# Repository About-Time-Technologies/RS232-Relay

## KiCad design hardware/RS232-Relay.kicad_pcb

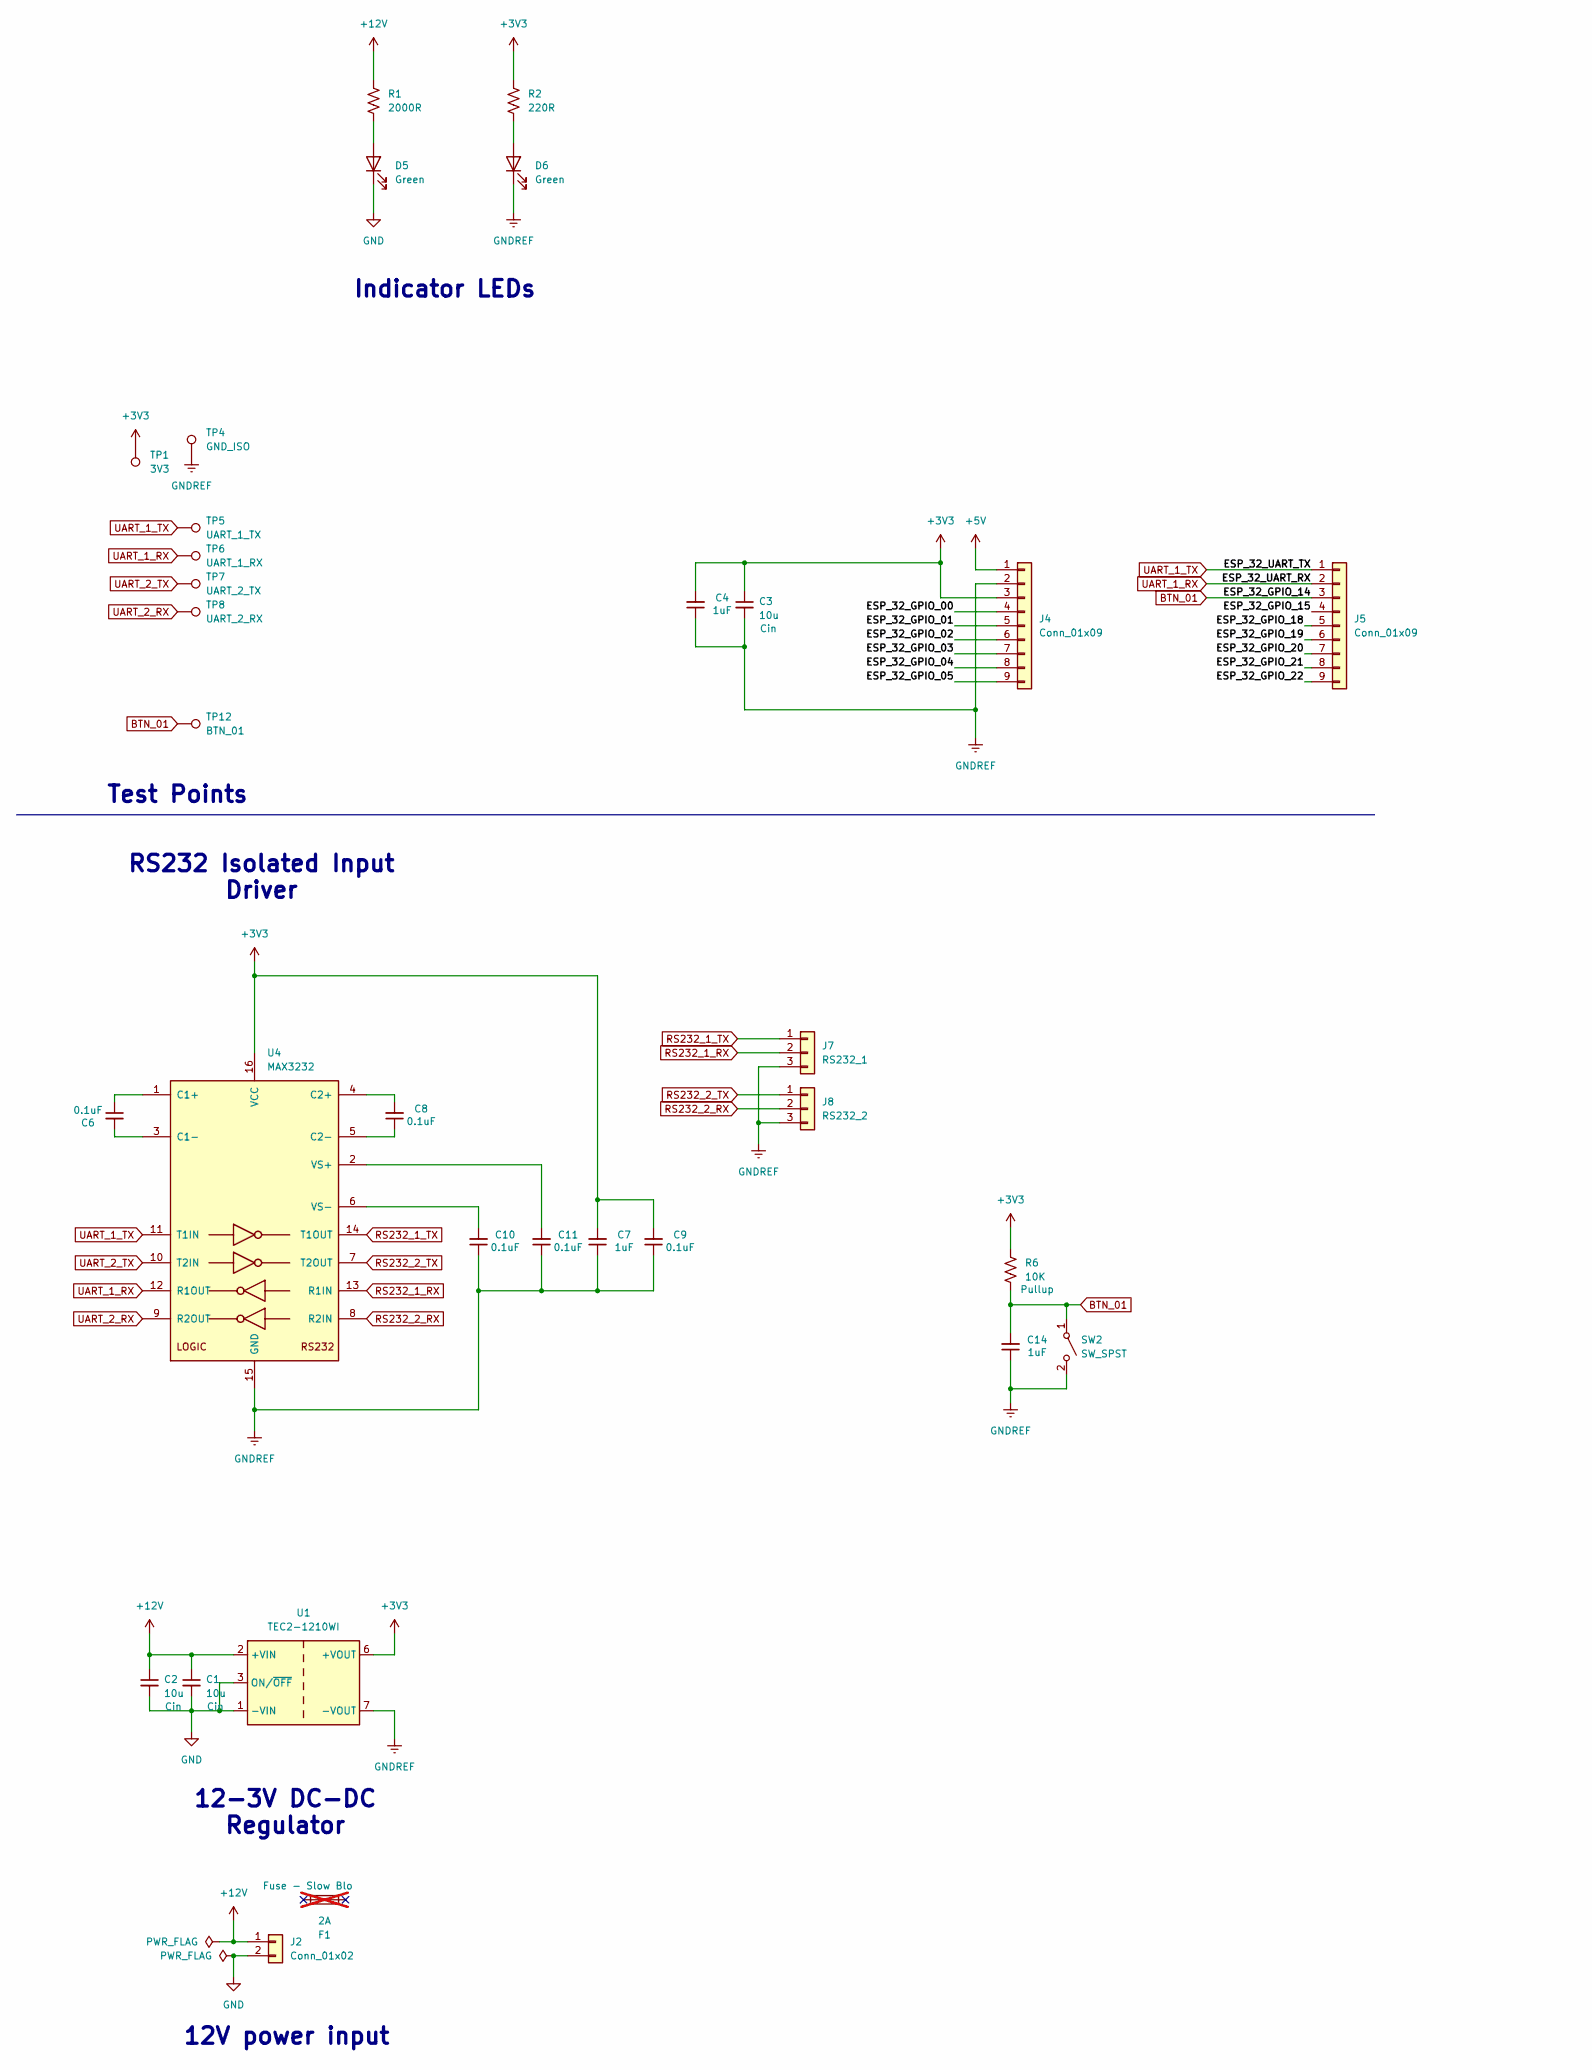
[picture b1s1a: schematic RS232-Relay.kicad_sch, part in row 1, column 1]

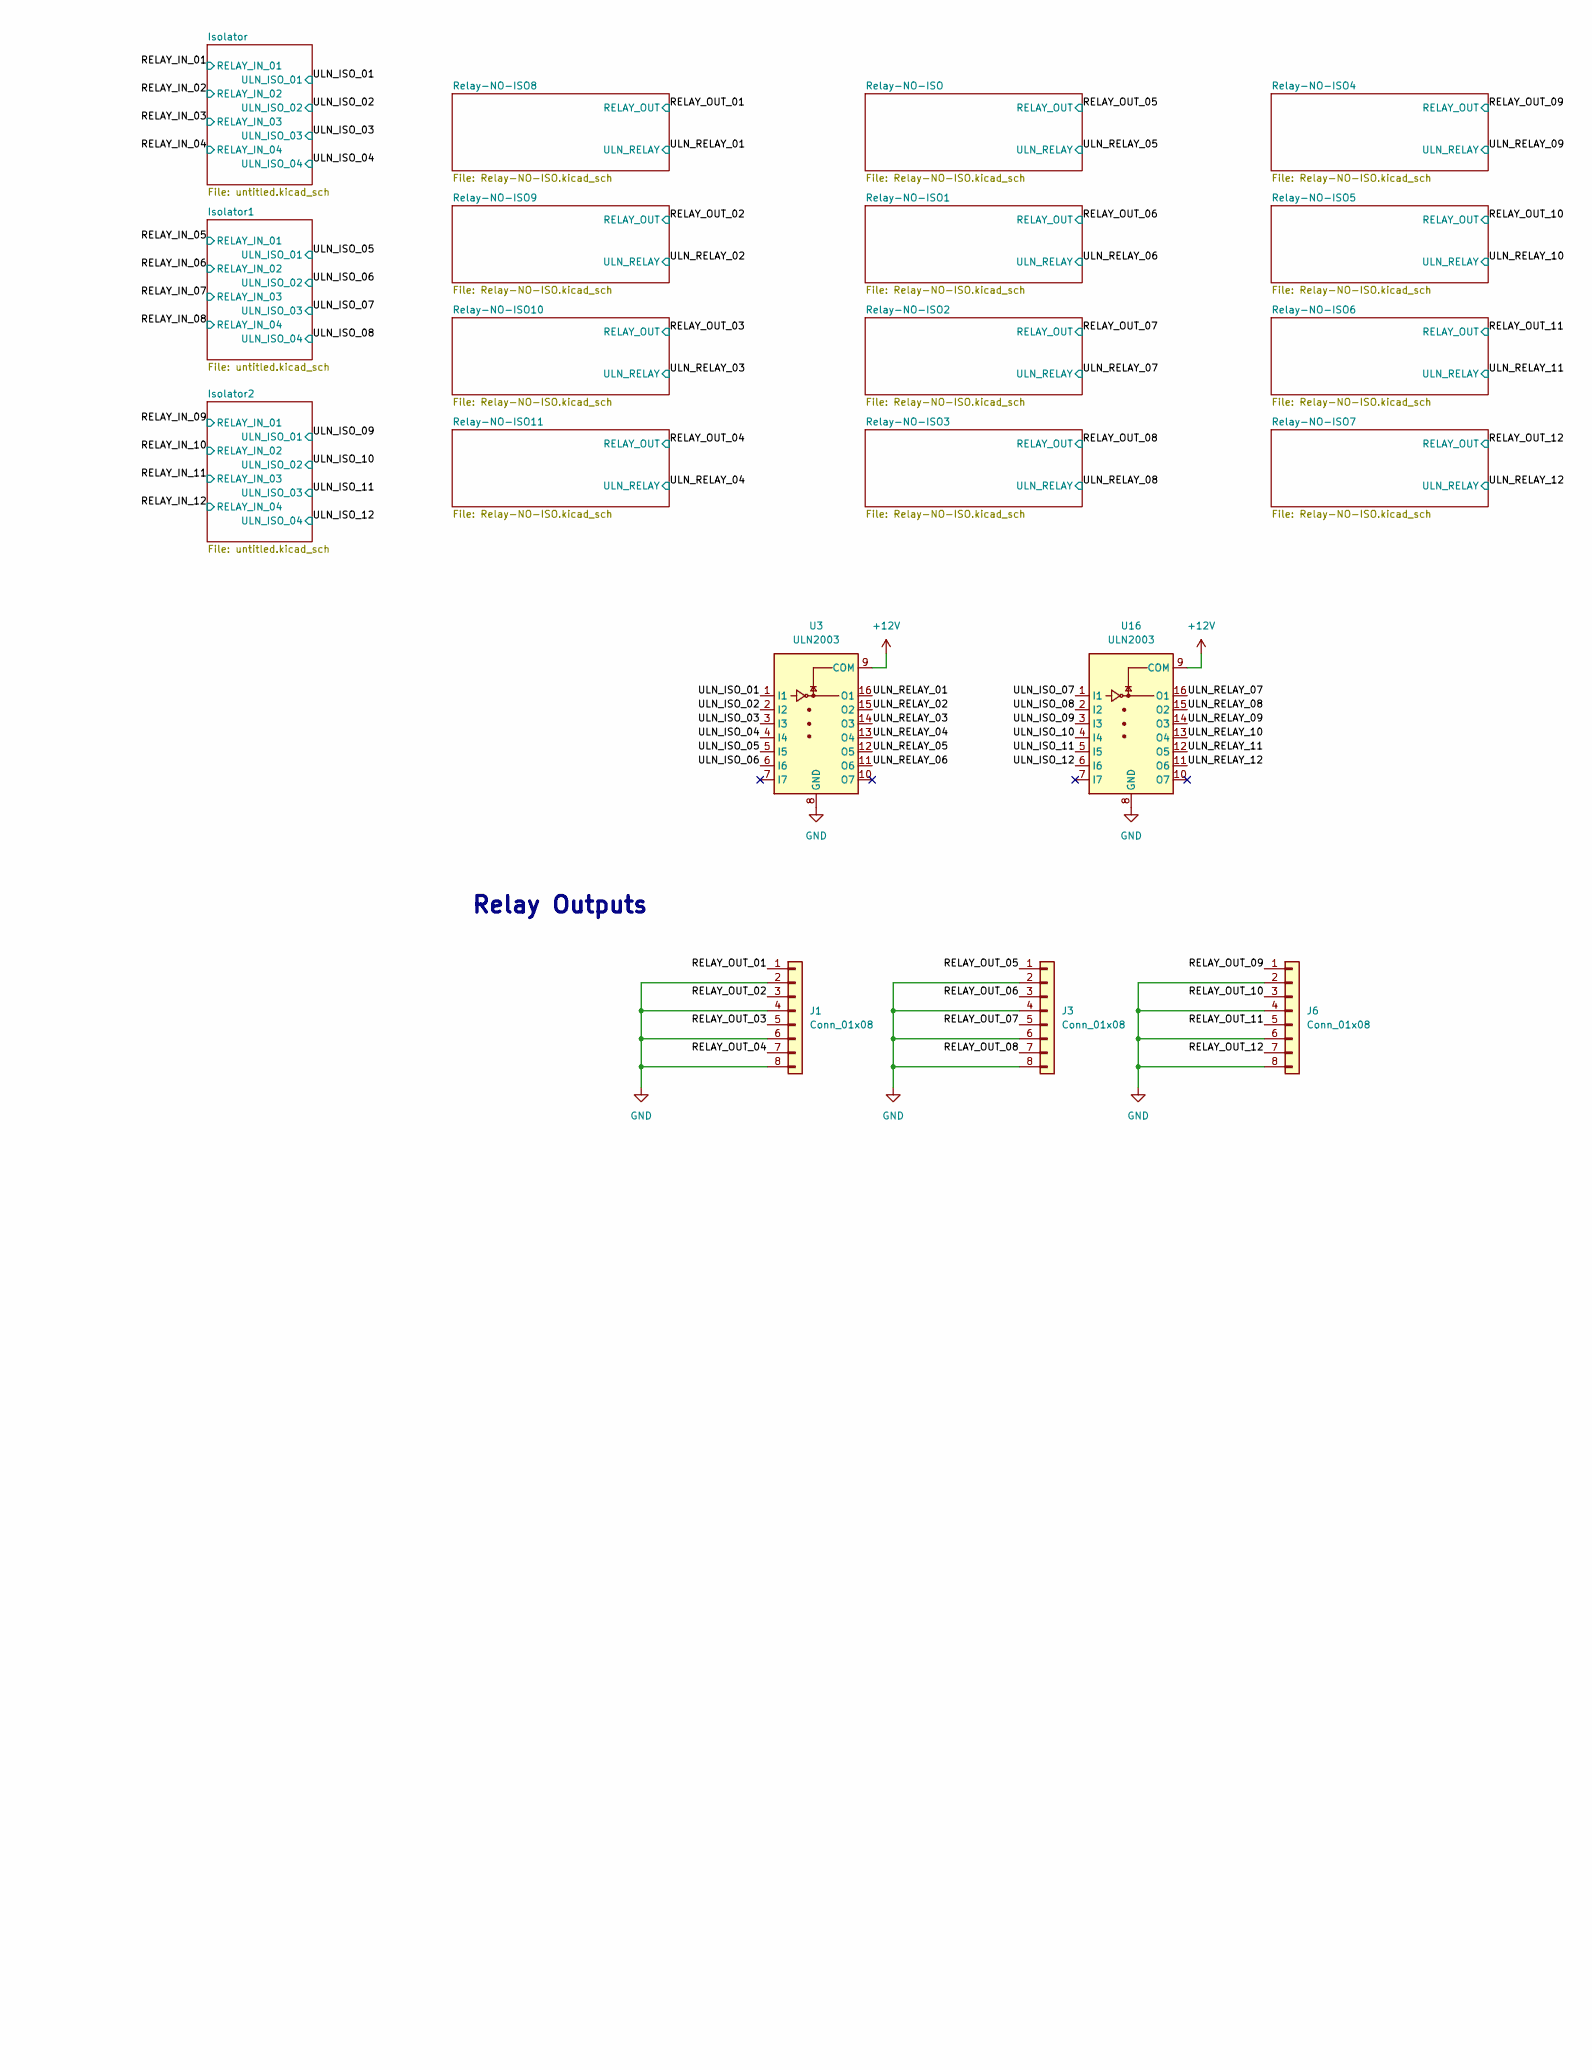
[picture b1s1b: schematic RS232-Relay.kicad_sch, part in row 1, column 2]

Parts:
C1, C2, C3: 10u; C_0603_1608Metric; LCSC C19702
C4, C7, C14: 1uF; C_0402_1005Metric; LCSC C52923
C6, C8, C9, C10, C11: 0.1uF; C_0402_1005Metric; LCSC C307331
D5, D6: Green; LED_0805_2012Metric; LCSC C2297
F1: 2A; Fuseholder_Littelfuse_Nano2_154x; not fitted
J1, J3, J6: Conn_01x08; PhoenixContact_MSTBA_2,5_8-G-5,08_1x08_P5.08mm_Horizontal
J2: Conn_01x02; PhoenixContact_MSTBA_2,5_2-G-5,08_1x02_P5.08mm_Horizontal
J4, J5: Conn_01x09; PinSocket_1x09_P2.54mm_Vertical
J7: RS232_1; PhoenixContact_MSTBA_2,5_3-G-5,08_1x03_P5.08mm_Horizontal
J8: RS232_2; PhoenixContact_MSTBA_2,5_3-G-5,08_1x03_P5.08mm_Horizontal
R1: 2000R; R_0603_1608Metric; LCSC C22975
R2: 220R; R_0603_1608Metric; LCSC C22962
R6: 10K; R_0402_1005Metric; LCSC C25744
SW2: SW_SPST; SW_PUSH_1P1T_6x3.5mm_H4.3_APEM_MJTP1243
TP1: 3V3; TestPoint_Pad_D1.0mm
TP4: GND_ISO; TestPoint_Pad_D1.0mm
TP5: UART_1_TX; TestPoint_Pad_D1.0mm
TP6: UART_1_RX; TestPoint_Pad_D1.0mm
TP7: UART_2_TX; TestPoint_Pad_D1.0mm
TP8: UART_2_RX; TestPoint_Pad_D1.0mm
TP12: BTN_01; TestPoint_Pad_D1.0mm
U1: TEC2-1210WI; Converter_DCDC_TRACO_TMR-xxxx_THT
U3, U16: ULN2003; DIP-16_W7.62mm_SMDSocket_SmallPads; LCSC C2690547
U4: MAX3232; TSSOP-16_4.4x5mm_P0.65mm

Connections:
+3V3: C3.1, C4.2, C7.2, C9.2, J4.3, R2.1, R6.1, TP1.1, U1.6 (+VOUT), U4.16 (VCC)
+5V: J4.1
+12V: C1.1, C2.1, J2.1, R1.1, U1.2 (+VIN), U3.9 (COM), U16.9 (COM); also elsewhere on the board
/ESP_32_GPIO_00: J4.4
/ESP_32_GPIO_01: J4.5
/ESP_32_GPIO_02: J4.6
/ESP_32_GPIO_03: J4.7
/ESP_32_GPIO_04: J4.8
/ESP_32_GPIO_05: J4.9
/ESP_32_GPIO_15: J5.4
/ESP_32_GPIO_18: J5.5
/ESP_32_GPIO_19: J5.6
/ESP_32_GPIO_20: J5.7
/ESP_32_GPIO_21: J5.8
/ESP_32_GPIO_22: J5.9
/RELAY_OUT_01: J1.1; also elsewhere on the board
/RELAY_OUT_02: J1.3; also elsewhere on the board
/RELAY_OUT_03: J1.5; also elsewhere on the board
/RELAY_OUT_04: J1.7; also elsewhere on the board
/RELAY_OUT_05: J3.1; also elsewhere on the board
/RELAY_OUT_06: J3.3; also elsewhere on the board
/RELAY_OUT_07: J3.5; also elsewhere on the board
/RELAY_OUT_08: J3.7; also elsewhere on the board
/RELAY_OUT_09: J6.1; also elsewhere on the board
/RELAY_OUT_10: J6.3; also elsewhere on the board
/RELAY_OUT_11: J6.5; also elsewhere on the board
/RELAY_OUT_12: J6.7; also elsewhere on the board
/ULN_ISO_01: U3.1 (I1); also elsewhere on the board
/ULN_ISO_02: U3.2 (I2); also elsewhere on the board
/ULN_ISO_03: U3.3 (I3); also elsewhere on the board
/ULN_ISO_04: U3.4 (I4); also elsewhere on the board
/ULN_ISO_05: U3.5 (I5); also elsewhere on the board
/ULN_ISO_06: U3.6 (I6); also elsewhere on the board
/ULN_ISO_07: U16.1 (I1); also elsewhere on the board
/ULN_ISO_08: U16.2 (I2); also elsewhere on the board
/ULN_ISO_09: U16.3 (I3); also elsewhere on the board
/ULN_ISO_10: U16.4 (I4); also elsewhere on the board
/ULN_ISO_11: U16.5 (I5); also elsewhere on the board
/ULN_ISO_12: U16.6 (I6); also elsewhere on the board
/ULN_RELAY_01: U3.16 (O1); also elsewhere on the board
/ULN_RELAY_02: U3.15 (O2); also elsewhere on the board
/ULN_RELAY_03: U3.14 (O3); also elsewhere on the board
/ULN_RELAY_04: U3.13 (O4); also elsewhere on the board
/ULN_RELAY_05: U3.12 (O5); also elsewhere on the board
/ULN_RELAY_06: U3.11 (O6); also elsewhere on the board
/ULN_RELAY_07: U16.16 (O1); also elsewhere on the board
/ULN_RELAY_08: U16.15 (O2); also elsewhere on the board
/ULN_RELAY_09: U16.14 (O3); also elsewhere on the board
/ULN_RELAY_10: U16.13 (O4); also elsewhere on the board
/ULN_RELAY_11: U16.12 (O5); also elsewhere on the board
/ULN_RELAY_12: U16.11 (O6); also elsewhere on the board
BTN_01: C14.2, J5.3, R6.2, SW2.1 (A), TP12.1
GND: C1.2, C2.2, D5.1 (K), J1.2, J1.4, J1.6, J1.8, J2.2, J3.2, J3.4, J3.6, J3.8, J6.2, J6.4, J6.6, J6.8, U1.1 (-VIN), U1.3 (ON/~OFF), U3.8 (GND), U16.8 (GND); also elsewhere on the board
GNDREF: C3.2, C4.1, C7.1, C9.1, C10.1, C11.1, C14.1, D6.1 (K), J4.2, J7.3, J8.3, SW2.2 (B), TP4.1, U1.7 (-VOUT), U4.15 (GND); also elsewhere on the board
unnamed: D5.2 (A), R1.2
unnamed: D6.2 (A), R2.2
unnamed: C6.1, U4.1 (C1+)
unnamed: C6.2, U4.3 (C1-)
unnamed: C8.2, U4.4 (C2+)
unnamed: C8.1, U4.5 (C2-)
unnamed: C11.2, U4.2 (VS+)
unnamed: C10.2, U4.6 (VS-)
RS232_1_RX: J7.2, U4.13 (R1IN)
RS232_1_TX: J7.1, U4.14 (T1OUT)
RS232_2_RX: J8.2, U4.8 (R2IN)
RS232_2_TX: J8.1, U4.7 (T2OUT)
UART_1_RX: J5.2, TP6.1, U4.12 (R1OUT)
UART_1_TX: J5.1, TP5.1, U4.11 (T1IN)
UART_2_RX: TP8.1, U4.9 (R2OUT)
UART_2_TX: TP7.1, U4.10 (T2IN)

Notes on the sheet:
Relay Outputs
12-3V DC-DC Regulator
12V power input
RS232 Isolated Input Driver
Test Points
Indicator LEDs

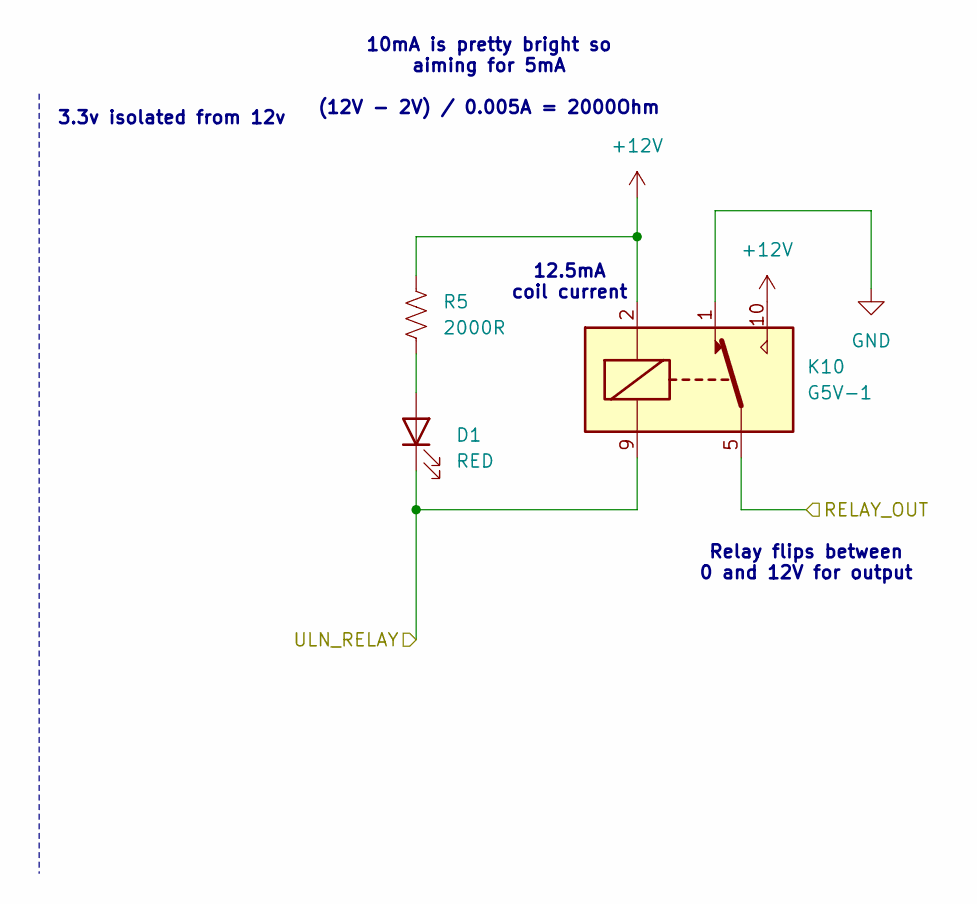
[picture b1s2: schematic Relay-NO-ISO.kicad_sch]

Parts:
D1: RED; LED_0805_2012Metric; LCSC C84256
K10: G5V-1; Relay_SPDT_Omron_G5V-1; LCSC C31113
R5: 2000R; R_0603_1608Metric; LCSC C22975

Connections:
+12V: K10.2, K10.10, R5.1; also elsewhere on the board
/RELAY_OUT_05: K10.5, K10.6; also elsewhere on the board
/ULN_RELAY_05: D1.1 (K), K10.9; also elsewhere on the board
GND: K10.1; also elsewhere on the board
unnamed: D1.2 (A), R5.2

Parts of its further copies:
D2, D3, D4, D7, D8, D9, D10, D11, D12, D13, D14: RED; LED_0805_2012Metric; LCSC C84256
K1, K2, K3, K4, K5, K6, K7, K8, K9, K11, K12: G5V-1; Relay_SPDT_Omron_G5V-1; LCSC C31113
R8, R10, R12, R14, R16, R18, R20, R22, R24, R26, R28: 2000R; R_0603_1608Metric; LCSC C22975

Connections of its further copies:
+12V: K1.2, K1.10, K2.2, K2.10, K3.2, K3.10, K4.2, K4.10, K5.2, K5.10, K6.2, K6.10, K7.2, K7.10, K8.2, K8.10, K9.2, K9.10, K11.2, K11.10, K12.2, K12.10, R8.1, R10.1, R12.1, R14.1, R16.1, R18.1, R20.1, R22.1, R24.1, R26.1, R28.1; also elsewhere on the board
/RELAY_OUT_01: K8.5, K8.6; also elsewhere on the board
/RELAY_OUT_02: K9.5, K9.6; also elsewhere on the board
/RELAY_OUT_03: K11.5, K11.6; also elsewhere on the board
/RELAY_OUT_04: K12.5, K12.6; also elsewhere on the board
/RELAY_OUT_06: K1.5, K1.6; also elsewhere on the board
/RELAY_OUT_07: K2.5, K2.6; also elsewhere on the board
/RELAY_OUT_08: K3.5, K3.6; also elsewhere on the board
/RELAY_OUT_09: K4.5, K4.6; also elsewhere on the board
/RELAY_OUT_10: K5.5, K5.6; also elsewhere on the board
/RELAY_OUT_11: K6.5, K6.6; also elsewhere on the board
/RELAY_OUT_12: K7.5, K7.6; also elsewhere on the board
/ULN_RELAY_01: D11.1 (K), K8.9; also elsewhere on the board
/ULN_RELAY_02: D12.1 (K), K9.9; also elsewhere on the board
/ULN_RELAY_03: D13.1 (K), K11.9; also elsewhere on the board
/ULN_RELAY_04: D14.1 (K), K12.9; also elsewhere on the board
/ULN_RELAY_06: D2.1 (K), K1.9; also elsewhere on the board
/ULN_RELAY_07: D3.1 (K), K2.9; also elsewhere on the board
/ULN_RELAY_08: D4.1 (K), K3.9; also elsewhere on the board
/ULN_RELAY_09: D7.1 (K), K4.9; also elsewhere on the board
/ULN_RELAY_10: D8.1 (K), K5.9; also elsewhere on the board
/ULN_RELAY_11: D9.1 (K), K6.9; also elsewhere on the board
/ULN_RELAY_12: D10.1 (K), K7.9; also elsewhere on the board
GND: K1.1, K2.1, K3.1, K4.1, K5.1, K6.1, K7.1, K8.1, K9.1, K11.1, K12.1; also elsewhere on the board
unnamed: D2.2 (A), R8.2
unnamed: D3.2 (A), R10.2
unnamed: D4.2 (A), R12.2
unnamed: D7.2 (A), R14.2
unnamed: D8.2 (A), R16.2
unnamed: D9.2 (A), R18.2
unnamed: D10.2 (A), R20.2
unnamed: D11.2 (A), R22.2
unnamed: D12.2 (A), R24.2
unnamed: D13.2 (A), R26.2
unnamed: D14.2 (A), R28.2

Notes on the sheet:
12.5mA coil current
3.3v isolated from 12v
Relay flips between 0 and 12V for output
10mA is pretty bright so aiming for 5mA (12V - 2V) / 0.005A = 2000Ohm

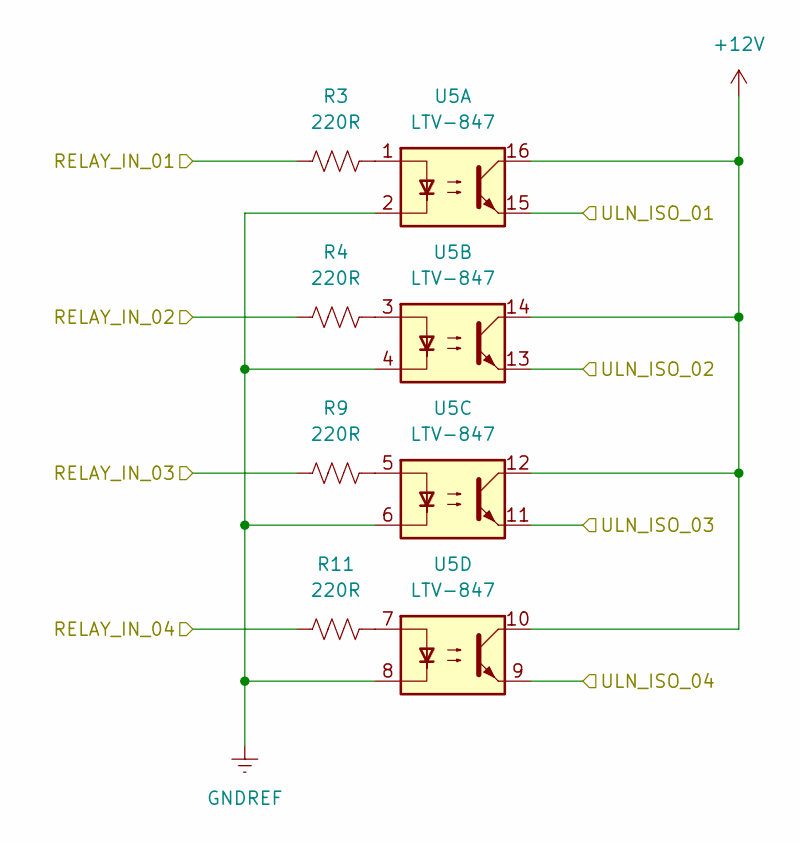
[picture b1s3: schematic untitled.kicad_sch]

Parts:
R3, R4, R9, R11: 220R; R_0603_1608Metric; LCSC C22962
U5: LTV-847; DIP-16_W7.62mm_SMDSocket_SmallPads

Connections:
+12V: U5.10, U5.12, U5.14, U5.16; also elsewhere on the board
/RELAY_IN_01: R3.1
/RELAY_IN_02: R4.1
/RELAY_IN_03: R9.1
/RELAY_IN_04: R11.1
/ULN_ISO_01: U5.15; also elsewhere on the board
/ULN_ISO_02: U5.13; also elsewhere on the board
/ULN_ISO_03: U5.11; also elsewhere on the board
/ULN_ISO_04: U5.9; also elsewhere on the board
GNDREF: U5.2, U5.4, U5.6, U5.8; also elsewhere on the board
unnamed: R3.2, U5.1
unnamed: R4.2, U5.3
unnamed: R9.2, U5.5
unnamed: R11.2, U5.7

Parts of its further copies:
R7, R13, R15, R17, R19, R21, R23, R25: 220R; R_0603_1608Metric; LCSC C22962
U2, U6: LTV-847; DIP-16_W7.62mm_SMDSocket_SmallPads

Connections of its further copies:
+12V: U2.10, U2.12, U2.14, U2.16, U6.10, U6.12, U6.14, U6.16; also elsewhere on the board
/RELAY_IN_05: R7.1
/RELAY_IN_06: R13.1
/RELAY_IN_07: R15.1
/RELAY_IN_08: R17.1
/RELAY_IN_09: R19.1
/RELAY_IN_10: R21.1
/RELAY_IN_11: R23.1
/RELAY_IN_12: R25.1
/ULN_ISO_05: U2.15; also elsewhere on the board
/ULN_ISO_06: U2.13; also elsewhere on the board
/ULN_ISO_07: U2.11; also elsewhere on the board
/ULN_ISO_08: U2.9; also elsewhere on the board
/ULN_ISO_09: U6.15; also elsewhere on the board
/ULN_ISO_10: U6.13; also elsewhere on the board
/ULN_ISO_11: U6.11; also elsewhere on the board
/ULN_ISO_12: U6.9; also elsewhere on the board
GNDREF: U2.2, U2.4, U2.6, U2.8, U6.2, U6.4, U6.6, U6.8; also elsewhere on the board
unnamed: R7.2, U2.1
unnamed: R13.2, U2.3
unnamed: R15.2, U2.5
unnamed: R17.2, U2.7
unnamed: R19.2, U6.1
unnamed: R21.2, U6.3
unnamed: R23.2, U6.5
unnamed: R25.2, U6.7

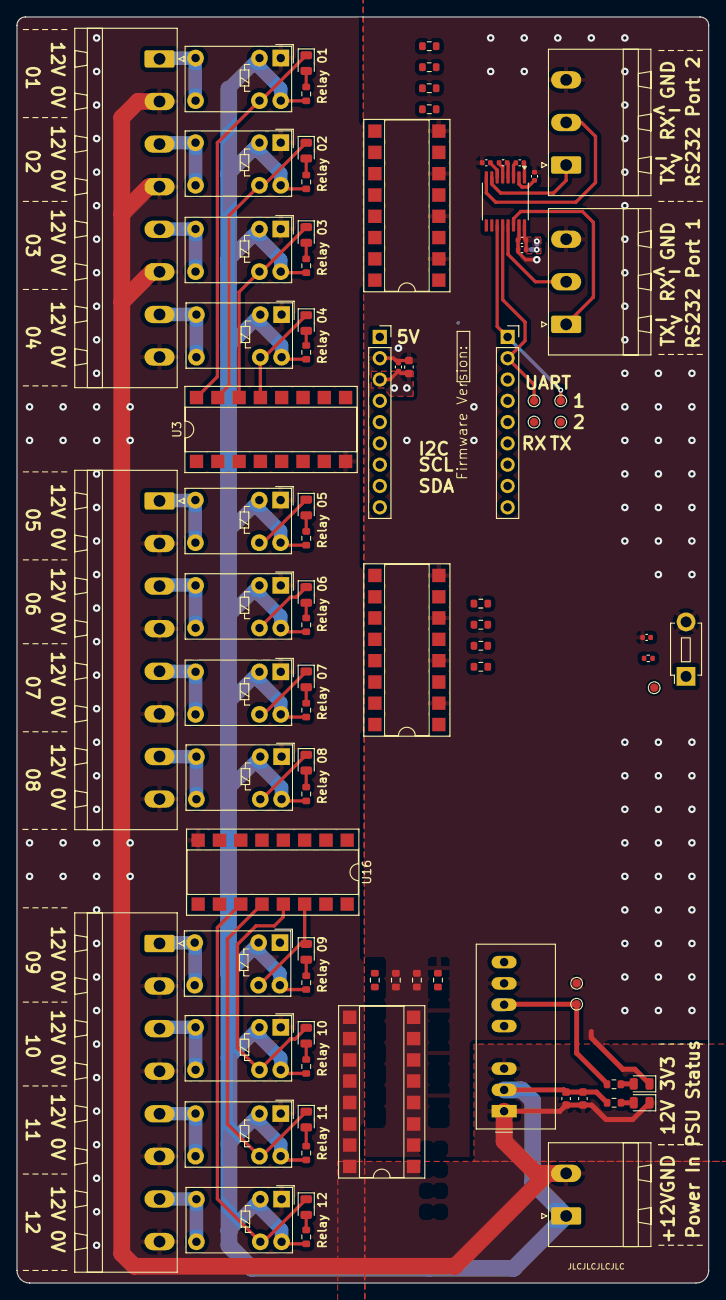
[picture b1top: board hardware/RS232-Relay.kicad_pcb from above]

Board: 2 copper layers, 82.5 x 151.0 mm, 87 parts (0 on the bottom side), 81 nets.

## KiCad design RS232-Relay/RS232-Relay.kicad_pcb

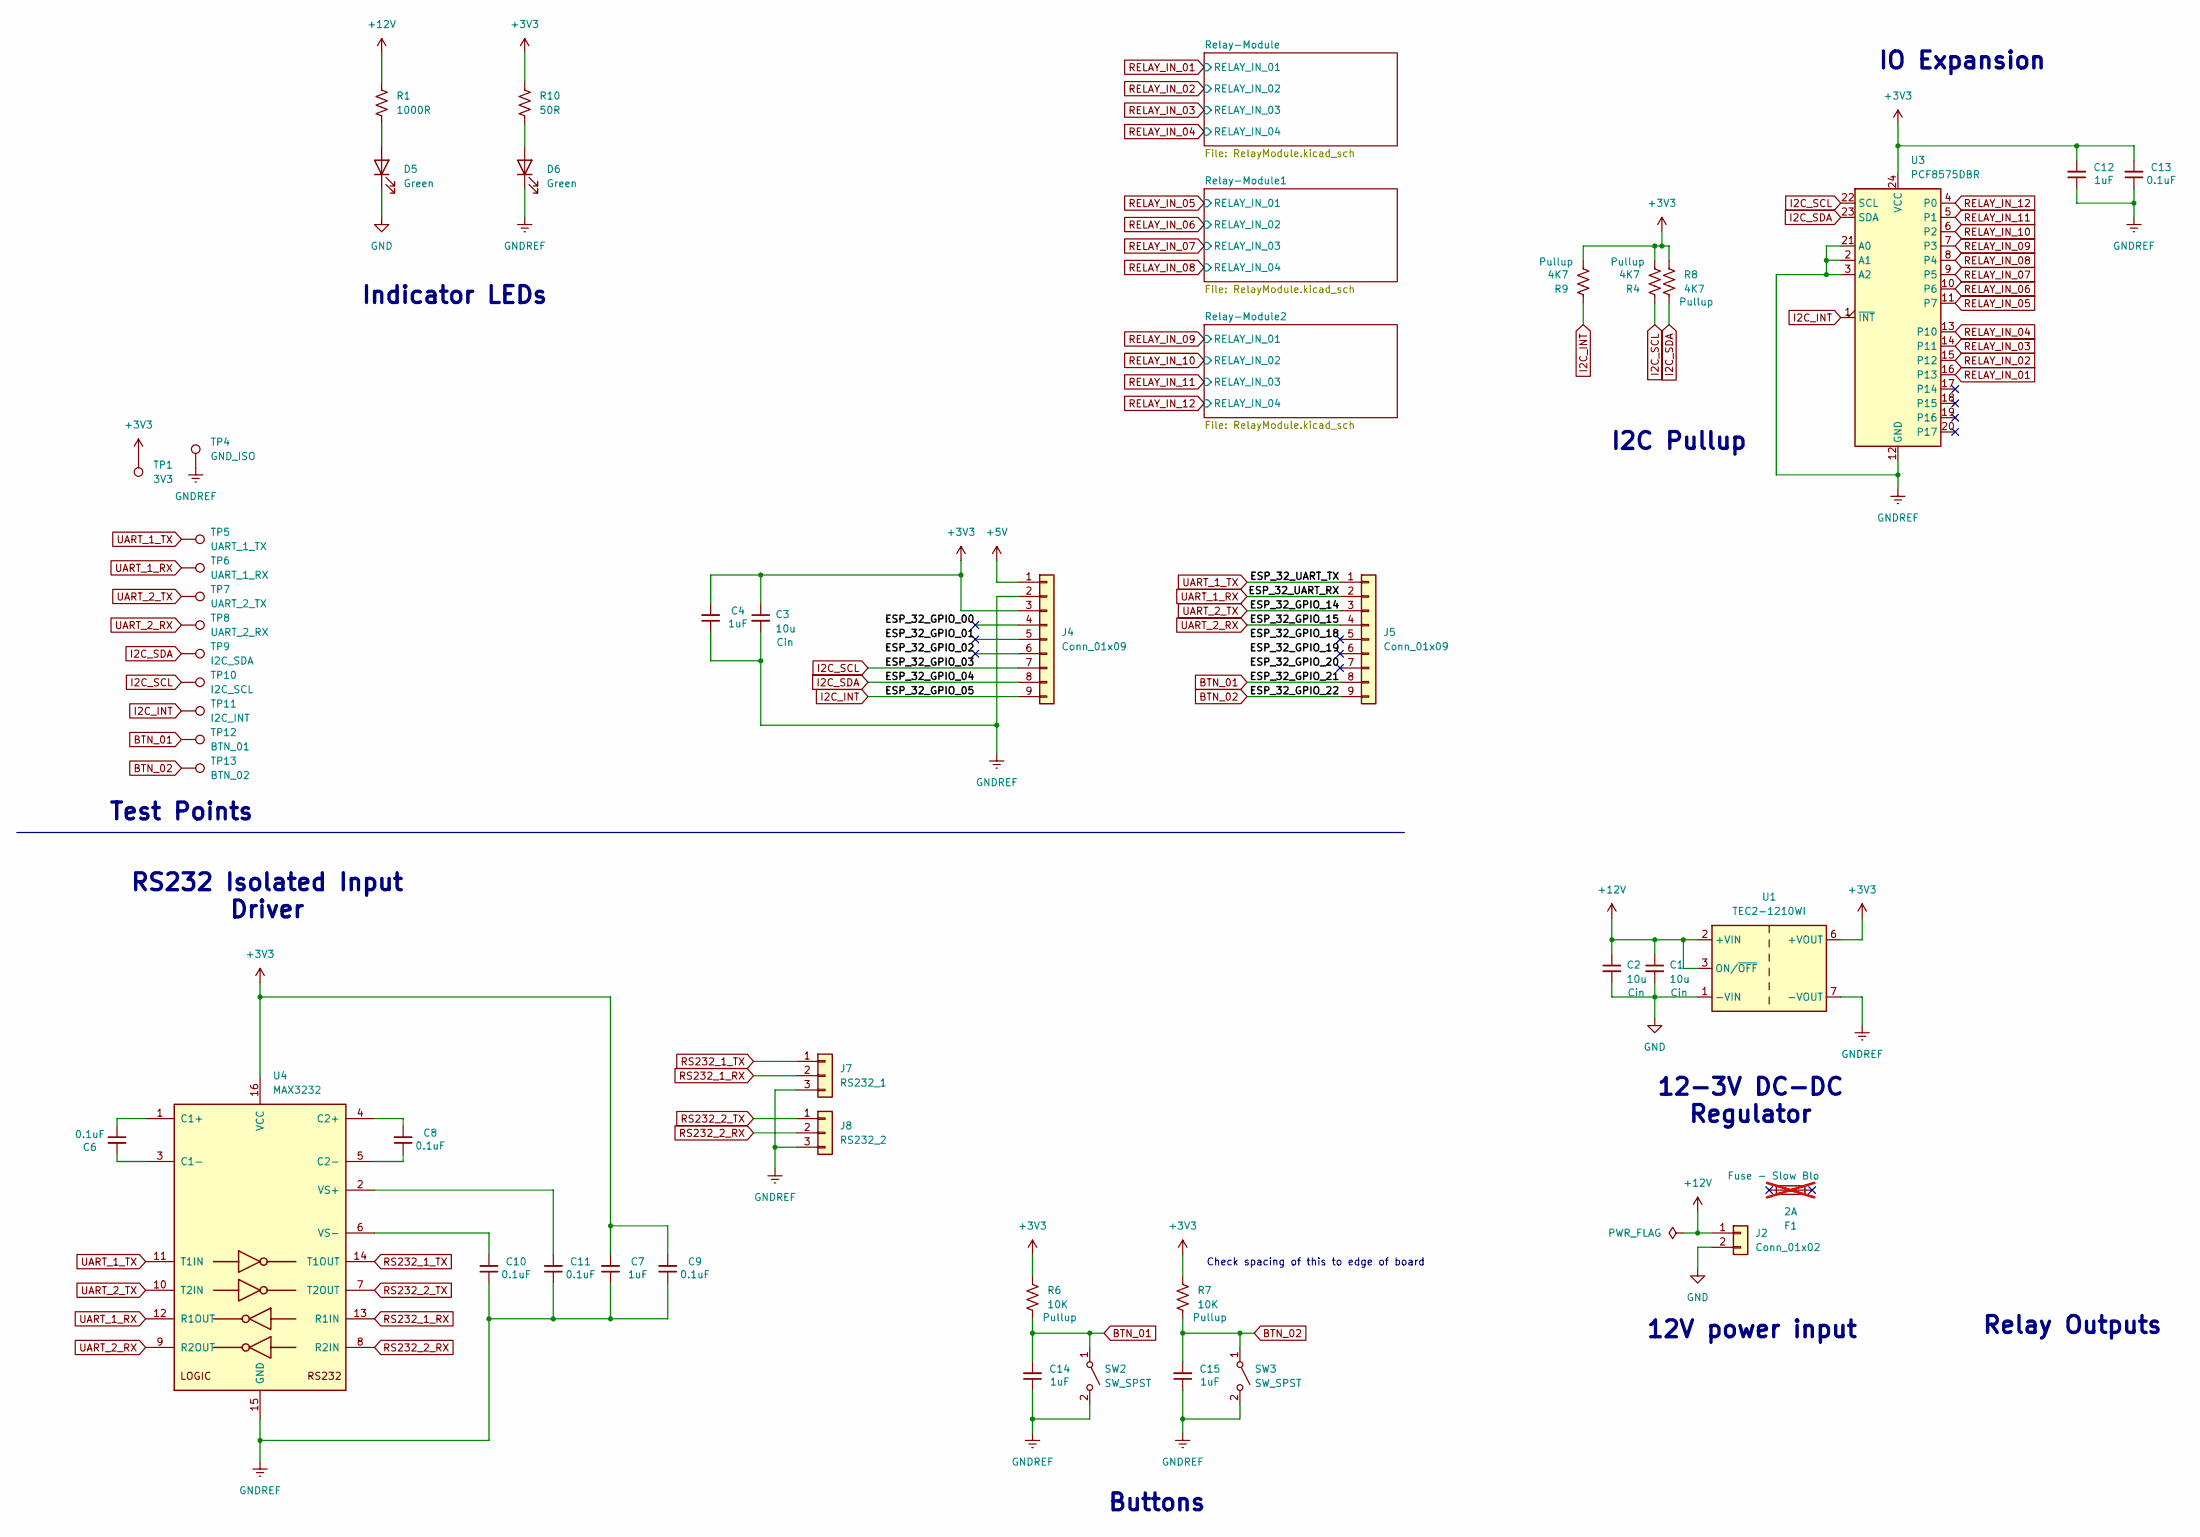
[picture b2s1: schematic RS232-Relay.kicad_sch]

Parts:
C1, C2, C3: 10u; C_0603_1608Metric; LCSC C19702
C4, C7, C12, C14, C15: 1uF; C_0402_1005Metric; LCSC C52923
C6, C8, C9, C10, C11, C13: 0.1uF; C_0402_1005Metric; LCSC C307331
D5, D6: Green; LED_0805_2012Metric; LCSC C2297
F1: 2A; Fuseholder_Littelfuse_Nano2_154x; not fitted
J2: Conn_01x02; PhoenixContact_MSTBA_2,5_2-G-5,08_1x02_P5.08mm_Horizontal
J4, J5: Conn_01x09; PinSocket_1x09_P2.54mm_Vertical
J7: RS232_1; PhoenixContact_MSTBA_2,5_3-G-5,08_1x03_P5.08mm_Horizontal
J8: RS232_2; PhoenixContact_MSTBA_2,5_3-G-5,08_1x03_P5.08mm_Horizontal
R1: 1000R; R_0603_1608Metric; LCSC C21190
R4, R8, R9: 4K7; R_0603_1608Metric; LCSC C23162
R6, R7: 10K; R_0402_1005Metric; LCSC C25744
R10: 50R; R_0603_1608Metric; LCSC C23197
SW2, SW3: SW_SPST; PTS841
TP1: 3V3; TestPoint_Pad_D1.0mm
TP4: GND_ISO; TestPoint_Pad_D1.0mm
TP5: UART_1_TX; TestPoint_Pad_D1.0mm
TP6: UART_1_RX; TestPoint_Pad_D1.0mm
TP7: UART_2_TX; TestPoint_Pad_D1.0mm
TP8: UART_2_RX; TestPoint_Pad_D1.0mm
TP9: I2C_SDA; TestPoint_Pad_D1.0mm
TP10: I2C_SCL; TestPoint_Pad_D1.0mm
TP11: I2C_INT; TestPoint_Pad_D1.0mm
TP12: BTN_01; TestPoint_Pad_D1.0mm
TP13: BTN_02; TestPoint_Pad_D1.0mm
U1: TEC2-1210WI; Converter_DCDC_TRACO_TMR-xxxx_THT
U3: PCF8575DBR; SSOP-24_5.3x8.2mm_P0.65mm
U4: MAX3232; TSSOP-16_4.4x5mm_P0.65mm

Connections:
+3V3: C3.1, C4.2, C7.2, C9.2, C12.2, C13.2, J4.3, R4.2, R6.1, R7.1, R8.1, R9.2, R10.2, TP1.1, U1.6 (+VOUT), U3.24 (VCC), U4.16 (VCC); also elsewhere on the board
+5V: J4.1
+12V: C1.1, C2.1, J2.1, R1.1, U1.2 (+VIN), U1.3 (ON/~OFF); also elsewhere on the board
/ESP_32_GPIO_00: J4.4
/ESP_32_GPIO_01: J4.5
/ESP_32_GPIO_02: J4.6
/ESP_32_GPIO_18: J5.5
/ESP_32_GPIO_19: J5.6
/ESP_32_GPIO_20: J5.7
BTN_01: C14.2, J5.8, R6.2, SW2.1 (A), TP12.1
BTN_02: C15.2, J5.9, R7.2, SW3.1 (A), TP13.1
GND: C1.2, C2.2, D5.1 (K), J2.2, U1.1 (-VIN); also elsewhere on the board
GNDREF: C3.2, C4.1, C7.1, C9.1, C10.1, C11.1, C12.1, C13.1, C14.1, C15.1, D6.1 (K), J4.2, J7.3, J8.3, SW2.2 (B), SW3.2 (B), TP4.1, U1.7 (-VOUT), U3.2 (A1), U3.3 (A2), U3.12 (GND), U3.21 (A0), U4.15 (GND)
I2C_INT: J4.9, R9.1, TP11.1, U3.1 (~INT)
I2C_SCL: J4.7, R4.1, TP10.1, U3.22 (SCL)
I2C_SDA: J4.8, R8.2, TP9.1, U3.23 (SDA)
unnamed: D5.2 (A), R1.2
unnamed: D6.2 (A), R10.1
unnamed: C6.1, U4.1 (C1+)
unnamed: C6.2, U4.3 (C1-)
unnamed: C8.2, U4.4 (C2+)
unnamed: C8.1, U4.5 (C2-)
unnamed: C11.2, U4.2 (VS+)
unnamed: C10.2, U4.6 (VS-)
RELAY_IN_01: U3.16 (P13); also elsewhere on the board
RELAY_IN_02: U3.15 (P12); also elsewhere on the board
RELAY_IN_03: U3.14 (P11); also elsewhere on the board
RELAY_IN_04: U3.13 (P10); also elsewhere on the board
RELAY_IN_05: U3.11 (P7); also elsewhere on the board
RELAY_IN_06: U3.10 (P6); also elsewhere on the board
RELAY_IN_07: U3.9 (P5); also elsewhere on the board
RELAY_IN_08: U3.8 (P4); also elsewhere on the board
RELAY_IN_09: U3.7 (P3); also elsewhere on the board
RELAY_IN_10: U3.6 (P2); also elsewhere on the board
RELAY_IN_11: U3.5 (P1); also elsewhere on the board
RELAY_IN_12: U3.4 (P0); also elsewhere on the board
RS232_1_RX: J7.2, U4.13 (R1IN)
RS232_1_TX: J7.1, U4.14 (T1OUT)
RS232_2_RX: J8.2, U4.8 (R2IN)
RS232_2_TX: J8.1, U4.7 (T2OUT)
UART_1_RX: J5.2, TP6.1, U4.12 (R1OUT)
UART_1_TX: J5.1, TP5.1, U4.11 (T1IN)
UART_2_RX: J5.4, TP8.1, U4.9 (R2OUT)
UART_2_TX: J5.3, TP7.1, U4.10 (T2IN)

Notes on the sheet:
IO Expansion
Relay Outputs
12-3V DC-DC Regulator
I2C Pullup
Check spacing of this to edge of board
12V power input
RS232 Isolated Input Driver
Buttons
Test Points
Indicator LEDs
